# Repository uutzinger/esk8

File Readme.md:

# Building Electric Skateboard

## [Wires and Connectors](Wire_Connectors.md)

## [Skateboard Design](ElectricSkateBoard.md)

## [Current limitting anti spark switch](Switch.md)

## [ODrive Setup](ODrive_v3.md)

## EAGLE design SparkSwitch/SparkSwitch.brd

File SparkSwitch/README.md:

# SparkSwitch
https://github.com/vedderb/SparkSwitch

Have a look at this thread:
https://endless-sphere.com/forums/viewtopic.php?f=3&t=40142&start=100

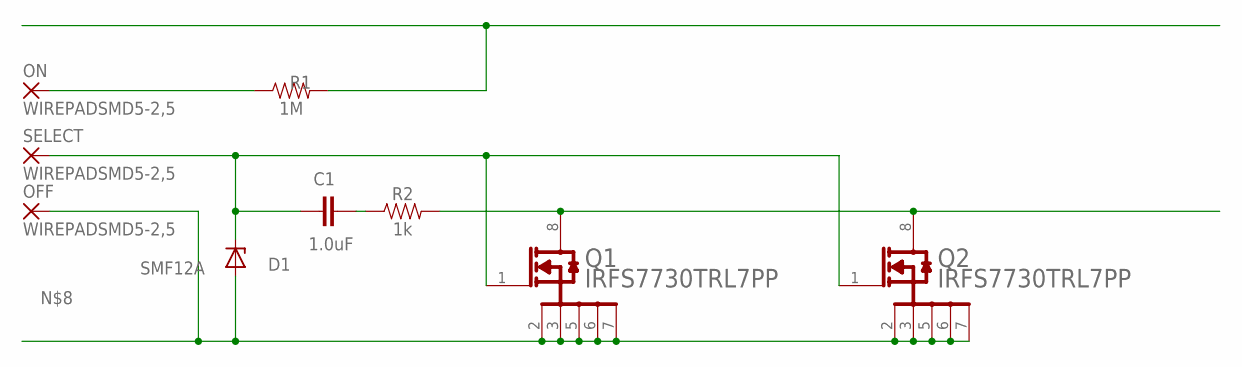
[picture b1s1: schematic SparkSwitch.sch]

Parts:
C1: 1.0uF; 0805
D1: SMF12A; SOD123F
OFF: WIREPADSMD5-2,5; 5-2,5
ON: WIREPADSMD5-2,5; 5-2,5
Q1, Q2: INFINEON_IRFS7730TRL7PPINFINEON_IRFS7730TRL7PP_0_0; INFINEON_IRFS7730TRL7PP_0
R1: 1M; 0603
R2: 1k; 0603
SELECT: WIREPADSMD5-2,5; 5-2,5

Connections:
unnamed: Q1.8 (D), Q2.8 (D), R2.2
unnamed: C1.1, D1.C, Q1.1 (G), Q2.1 (G), SELECT.1
unnamed: C1.2, R2.1
unnamed: ON.1, R1.1
unnamed: D1.A, OFF.1, Q1.2 (1_S), Q1.3 (2_S), Q1.5 (3_S), Q1.6 (4_S), Q1.7 (5_S), Q2.2 (1_S), Q2.3 (2_S), Q2.5 (3_S), Q2.6 (4_S), Q2.7 (5_S)

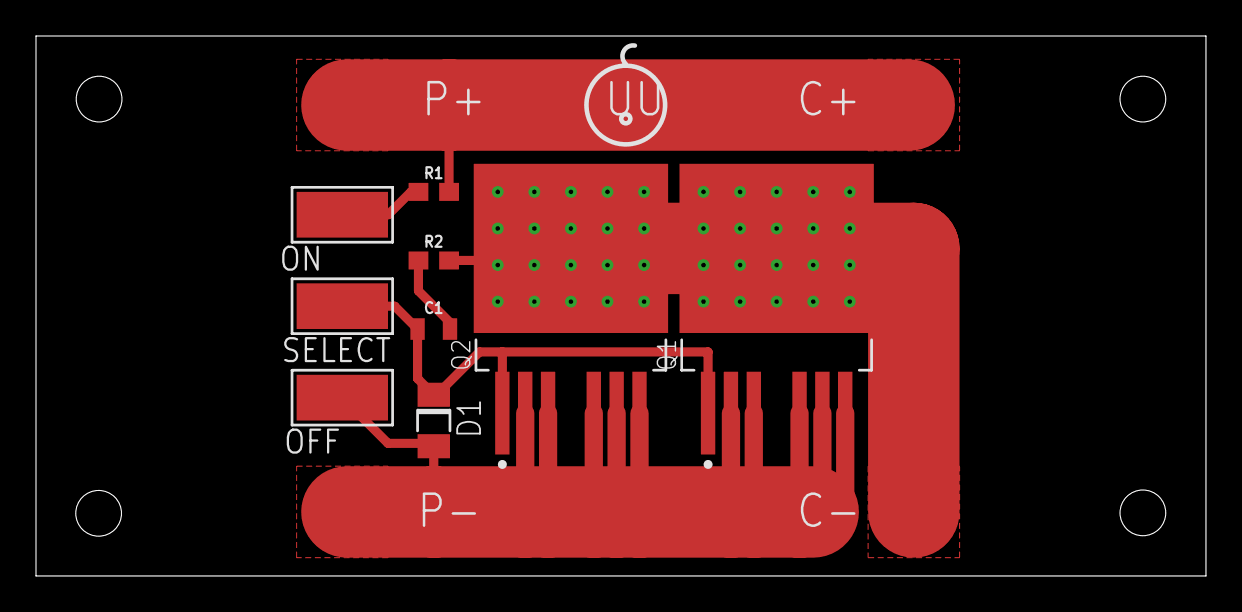
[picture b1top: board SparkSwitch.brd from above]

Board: 2 copper layers, 65.0 x 30.0 mm, 9 parts (0 on the bottom side), 5 nets.

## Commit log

2020-11-23 Some progress
2021-07-09 Deck Design
2021-12-22 Motor sensor wires
2023-04-30 latest
2023-04-30 Plot speed
2023-05-04 Functional release
2023-05-04 Rename GamePadPoll.py to GamePad.py
2023-05-05 Edits
2023-05-05 Cleanup and Comments
2023-09-05 ODrive Connections
2023-09-11 Odrive Tuning
2023-09-17 SparkSwitch
2023-09-20 Odrive Optimizations
2023-10-03 Rename ElectricScateBoard.md to ElectricSkateBoard.md
2023-10-03 Rename ODrive v3.md to ODrive_v3.md

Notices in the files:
parts and their libraries:
SparkFun-Capacitors: Licensing: Creative Commons ShareAlike 4.0 International - https://creativecommons.org/licenses/by-sa/4.0
